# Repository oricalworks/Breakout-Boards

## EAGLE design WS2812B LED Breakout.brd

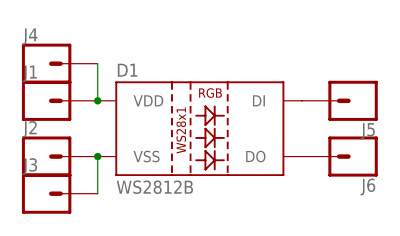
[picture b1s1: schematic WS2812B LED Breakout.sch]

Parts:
D1: WS2812B
J1, J2, J3, J4, J5, J6: CONN_01PTH_LONGPAD; 1X01_LONGPAD

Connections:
unnamed: D1.1 (VDD), J1.1, J4.1
unnamed: D1.3 (VSS), J2.1, J3.1
unnamed: D1.4 (DI), J5.1
unnamed: D1.2 (DO), J6.1

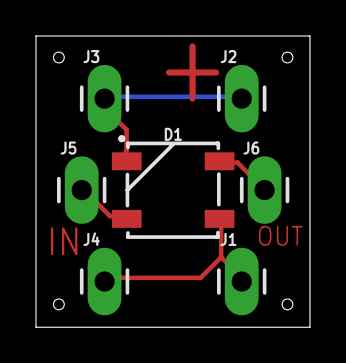
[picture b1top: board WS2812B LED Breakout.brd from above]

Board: 2 copper layers, 15.2 x 16.2 mm, 7 parts (0 on the bottom side), 4 nets.

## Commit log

2017-05-24 First Release

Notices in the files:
parts and their libraries:
SparkFun-LED: Licensing: Creative Commons ShareAlike 4.0 International - https://creativecommons.org/licenses/by-sa/4.0
